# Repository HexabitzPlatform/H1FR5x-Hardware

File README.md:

# H1FR50-Hardware
Hexabitz SAM-M10Q GNSS Module Hardware Design

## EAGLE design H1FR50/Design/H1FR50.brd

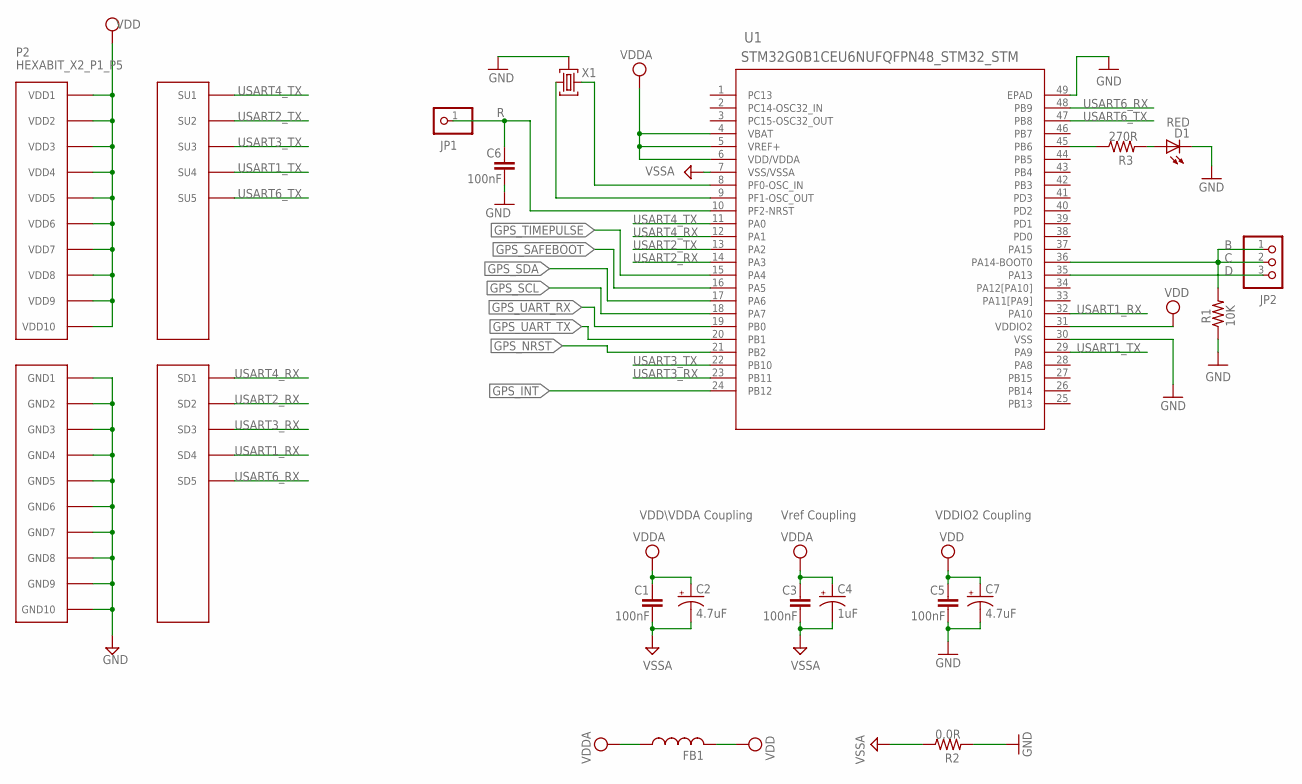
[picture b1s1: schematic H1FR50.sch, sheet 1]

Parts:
C1, C3, C5, C6: 100nF; C-0603
C2, C7: 4.7uF; C-0805-POL
C4: 1uF; C-0805-POL
D1: RED; VLMS1300-GS08
FB1: FB-0603
JP1: R; 1X01
JP2: PINHD-1X3; 1X03
P2: HEXABIT_X2_P1_P5; HEXABIT_17.32_X2_P1_P5
R1: 10K; R-0603
R2: 0.0R; R-0603
R3: 270R; R-0603
U1: STM32G0B1CEU6NUFQFPN48_STM32_STM; UFQFPN48_STM32_STM
X1: XTALL_CSTCE8M00G52

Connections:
C: JP2.1, JP2.2, R1.2, U1.36 (PA14-BOOT0)
D: JP2.3, U1.35 (PA13)
GND: C5.2, C6.2, C7.2 (-), D1.C, P2.PAD_PD11 (GND1), P2.PAD_PD12 (GND2), P2.PAD_PD13 (GND3), P2.PAD_PD14 (GND4), P2.PAD_PD15 (GND5), P2.PAD_PD16 (GND6), P2.PAD_PD17 (GND7), P2.PAD_PD18 (GND8), P2.PAD_PD19 (GND9), P2.PAD_PD20 (GND10), R1.1, R2.2, U1.30 (VSS), U1.49 (EPAD), X1.P$2 (2); also elsewhere on the board
GPS_INT: U1.24 (PB12); also elsewhere on the board
GPS_NRST: U1.21 (PB2); also elsewhere on the board
GPS_SAFEBOOT: U1.16 (PA5); also elsewhere on the board
GPS_SCL: U1.18 (PA7); also elsewhere on the board
GPS_SDA: U1.17 (PA6); also elsewhere on the board
GPS_TIMEPULSE: U1.15 (PA4); also elsewhere on the board
GPS_UART_RX: U1.19 (PB0); also elsewhere on the board
GPS_UART_TX: U1.20 (PB1); also elsewhere on the board
unnamed: D1.A, R3.2
unnamed: U1.8 (PF0-OSC_IN), X1.P$1 (1)
unnamed: U1.9 (PF1-OSC_OUT), X1.P$3 (3)
unnamed: C6.1, JP1.1, U1.10 (PF2-NRST)
unnamed: R3.1, U1.45 (PB6)
USART1_RX: P2.PAD_PD4 (SD4), U1.32 (PA10)
USART1_TX: P2.PAD_PU4 (SU4), U1.29 (PA9)
USART2_RX: P2.PAD_PD2 (SD2), U1.14 (PA3)
USART2_TX: P2.PAD_PU2 (SU2), U1.13 (PA2)
USART3_RX: P2.PAD_PD3 (SD3), U1.23 (PB11)
USART3_TX: P2.PAD_PU3 (SU3), U1.22 (PB10)
USART4_RX: P2.PAD_PD1 (SD1), U1.12 (PA1)
USART4_TX: P2.PAD_PU1 (SU1), U1.11 (PA0)
USART6_RX: P2.PAD_PD5 (SD5), U1.48 (PB9)
USART6_TX: P2.PAD_PU5 (SU5), U1.47 (PB8)
VDD: C5.1, C7.1 (+), FB1.2, P2.PAD_PU11 (VDD1), P2.PAD_PU12 (VDD2), P2.PAD_PU13 (VDD3), P2.PAD_PU14 (VDD4), P2.PAD_PU15 (VDD5), P2.PAD_PU16 (VDD6), P2.PAD_PU17 (VDD7), P2.PAD_PU18 (VDD8), P2.PAD_PU19 (VDD9), P2.PAD_PU20 (VDD10), U1.31 (VDDIO2); also elsewhere on the board
VDDA: C1.1, C2.1 (+), C3.1, C4.1 (+), FB1.1, U1.4 (VBAT), U1.5 (VREF+), U1.6 (VDD/VDDA)
VSSA: C1.2, C2.2 (-), C3.2, C4.2 (-), R2.1, U1.7 (VSS/VSSA)

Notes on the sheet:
Vref Coupling
VDDIO2 Coupling
VDD\VDDA Coupling

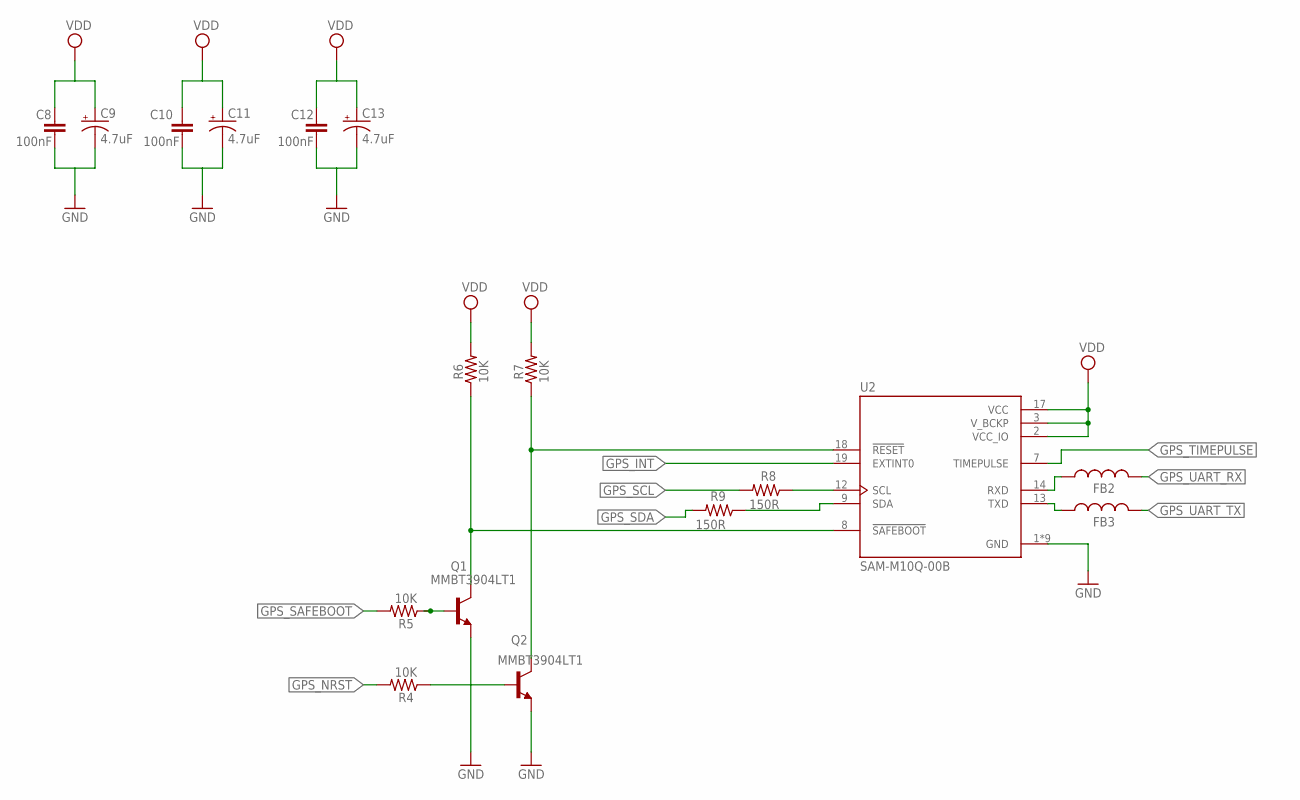
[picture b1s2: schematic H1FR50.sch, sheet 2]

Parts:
C8, C10, C12: 100nF; C-0603
C9, C11, C13: 4.7uF; C-0805-POL
FB2, FB3: BLM18KG601SN1D; FB-0603
Q1, Q2: MMBT3904LT1
R4, R5, R6, R7: 10K; R-0603
R8, R9: 150R; R-0603; MPN CRCW0603150RFKEA
U2: SAM-M8Q-0-10; MODULE_SAM-M8Q-0-10

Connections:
GND: C8.2, C9.2 (-), C10.2, C11.2 (-), C12.2, C13.2 (-), Q1.2 (E), Q2.2 (E), U2.1 (GND), U2.4 (GND), U2.5 (GND), U2.6 (GND), U2.10 (GND), U2.11 (GND), U2.15 (GND), U2.16 (GND), U2.20 (GND); also elsewhere on the board
GPS_INT: U2.19 (EXTINT0); also elsewhere on the board
GPS_NRST: R4.2; also elsewhere on the board
GPS_SAFEBOOT: R5.2; also elsewhere on the board
GPS_SCL: R8.2; also elsewhere on the board
GPS_SDA: R9.2; also elsewhere on the board
GPS_TIMEPULSE: U2.7 (TIMEPULSE); also elsewhere on the board
GPS_UART_RX: FB2.2; also elsewhere on the board
GPS_UART_TX: FB3.2; also elsewhere on the board
unnamed: Q2.3 (C), R7.1, U2.18 (!RESET)
unnamed: Q1.3 (C), R6.1, U2.8 (!SAFEBOOT)
unnamed: Q2.1 (B), R4.1
unnamed: Q1.1 (B), R5.1
unnamed: FB2.1, U2.14 (RXD)
unnamed: FB3.1, U2.13 (TXD)
unnamed: R8.1, U2.12 (SCL)
unnamed: R9.1, U2.9 (SDA)
VDD: C8.1, C9.1 (+), C10.1, C11.1 (+), C12.1, C13.1 (+), R6.2, R7.2, U2.2 (VCC_IO), U2.3 (V_BCKP), U2.17 (VCC); also elsewhere on the board

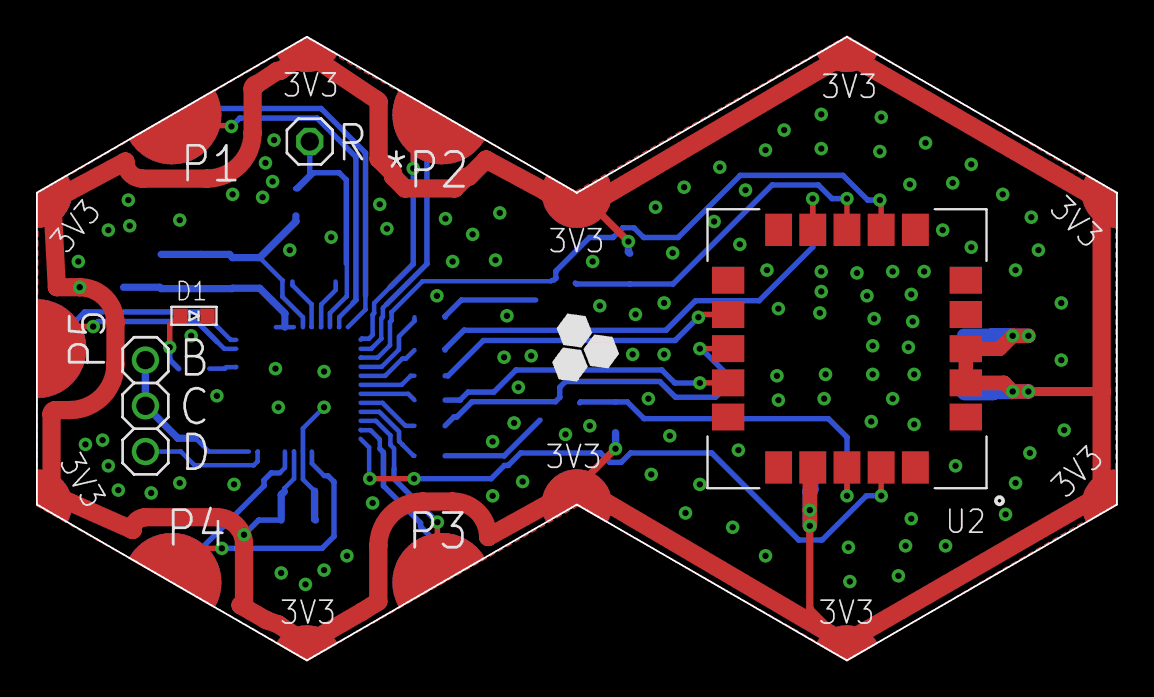
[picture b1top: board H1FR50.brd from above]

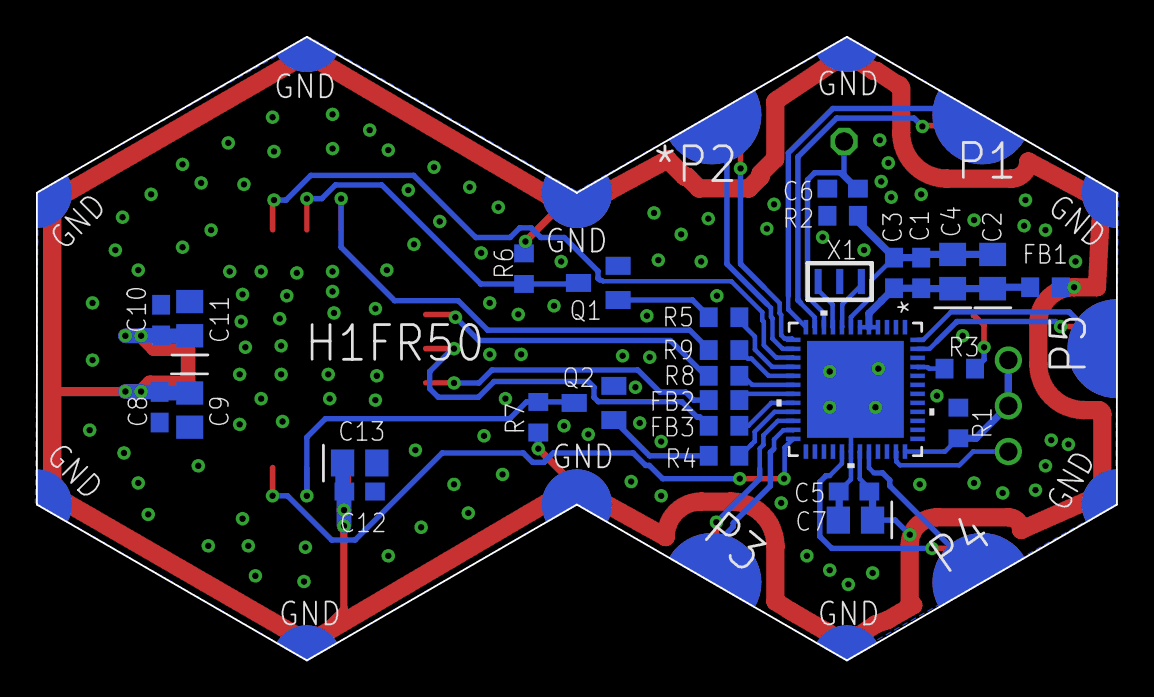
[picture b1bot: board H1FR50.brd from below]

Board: 2 copper layers, 60.0 x 34.6 mm, 34 parts (29 on the bottom side), 37 nets.

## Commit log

2023-09-28 -Update the GNSS Module (SAM-M10Q-00B) in BOM and Schematic files

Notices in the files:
parts and their libraries:
COPYRIGHT: Copyright (C) 2022 Ultra Librarian. All rights reserved.
